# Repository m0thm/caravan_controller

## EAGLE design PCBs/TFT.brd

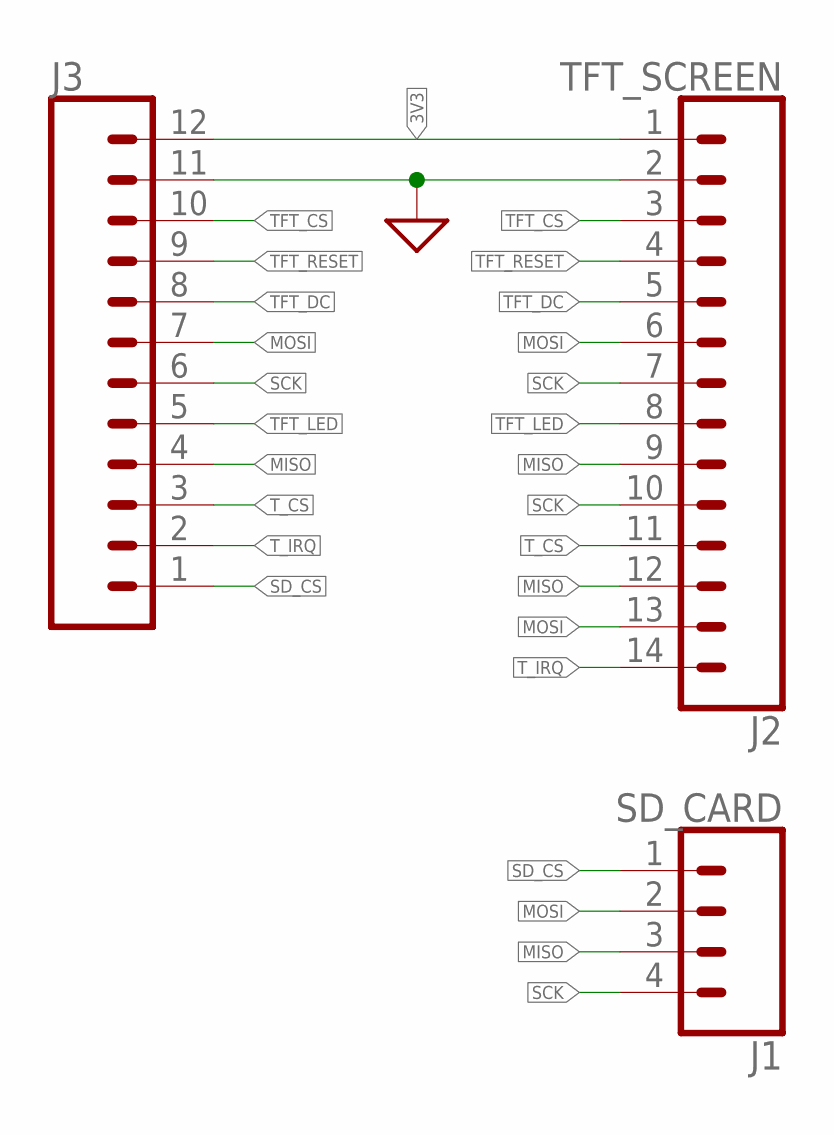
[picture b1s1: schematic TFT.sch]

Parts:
J1: SD_CARD; 1X04
J2: TFT_SCREEN; 1X14
J3: CONN_12; 1X12

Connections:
3V3: J2.1, J3.12
GND: J2.2, J3.11
MISO: J1.3, J2.9, J2.12, J3.4
MOSI: J1.2, J2.6, J2.13, J3.7
SCK: J1.4, J2.7, J2.10, J3.6
SD_CS: J1.1, J3.1
TFT_CS: J2.3, J3.10
TFT_DC: J2.5, J3.8
TFT_LED: J2.8, J3.5
TFT_RESET: J2.4, J3.9
T_CS: J2.11, J3.3
T_IRQ: J2.14, J3.2

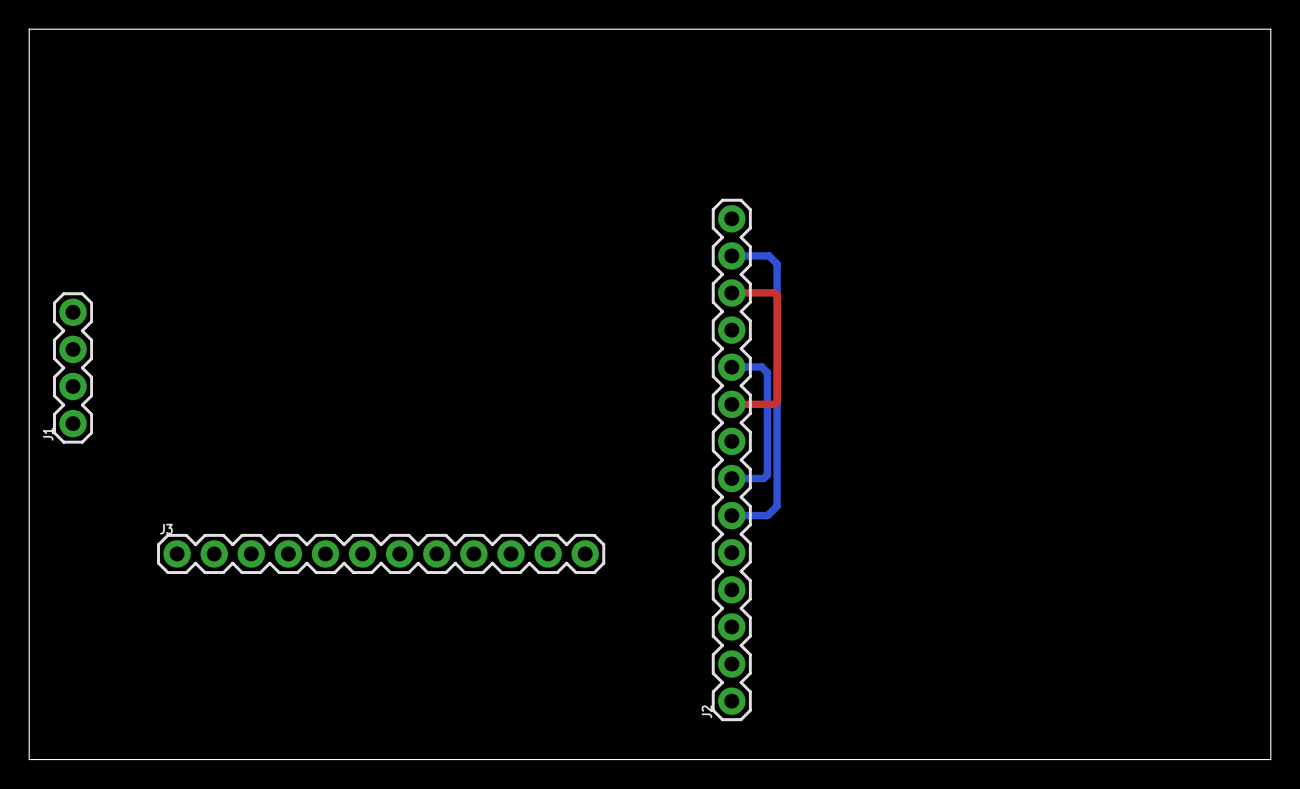
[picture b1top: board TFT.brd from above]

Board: 2 copper layers, 85.0 x 50.0 mm, 3 parts (0 on the bottom side), 12 nets.

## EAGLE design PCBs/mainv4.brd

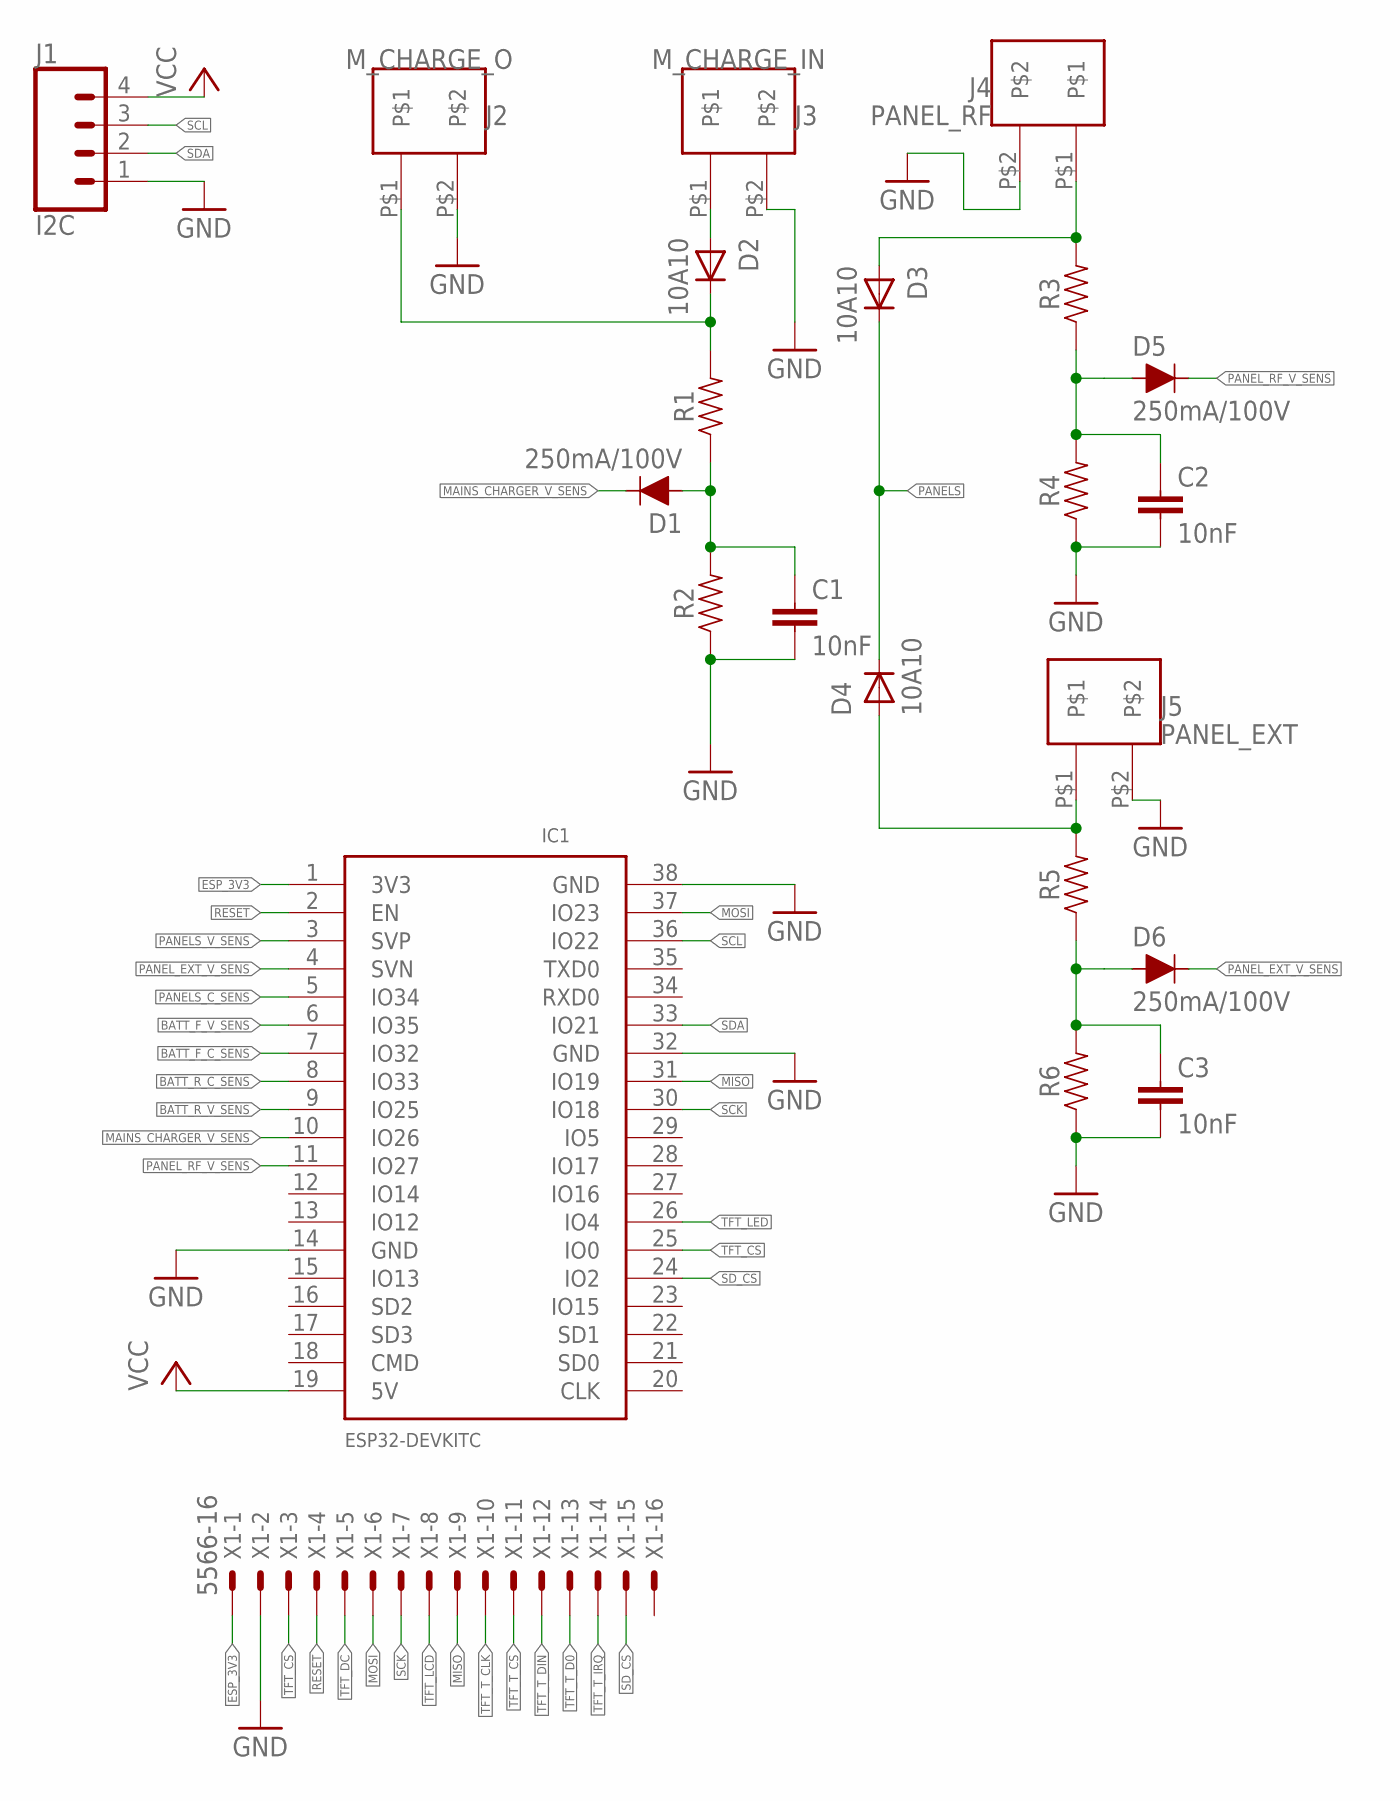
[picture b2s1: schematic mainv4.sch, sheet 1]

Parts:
C1, C2, C3: 10nF; 0603
D1, D5, D6: 250mA/100V; SOD-323
D2, D3, D4: 10A10; AG
IC1: ESP32DEVKITC; ESP32-DEVKITC
J1: I2C; MOLEX-1X4
J2: M_CHARGE_O; 40A-2PIN
J3: M_CHARGE_IN; 40A-2PIN
J4: PANEL_RF; 40A-2PIN
J5: PANEL_EXT; 40A-2PIN
R1, R2, R3, R4, R5, R6: 0805
X1: 5566-16

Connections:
BATT_F_C_SENS: IC1.7 (IO32); also elsewhere on the board
BATT_F_V_SENS: IC1.6 (IO35); also elsewhere on the board
BATT_R_C_SENS: IC1.8 (IO33); also elsewhere on the board
BATT_R_V_SENS: IC1.9 (IO25); also elsewhere on the board
ESP_3V3: IC1.1 (3V3), X1.1
GND: C1.2, C2.2, C3.2, IC1.14 (GND), IC1.32 (GND), IC1.38 (GND), J1.1, J2.P$2, J3.P$2, J4.P$2, J5.P$2, R2.1, R4.1, R6.1, X1.2; also elsewhere on the board
MAINS_CHARGER_V_SENS: D1.C, IC1.10 (IO26)
MISO: IC1.31 (IO19), X1.9
MOSI: IC1.37 (IO23), X1.6
unnamed: D2.A, J3.P$1
unnamed: D2.C, J2.P$1, R1.2
unnamed: D3.A, J4.P$1, R3.2
unnamed: C2.1, D5.A, R3.1, R4.2
unnamed: C3.1, D6.A, R5.1, R6.2
unnamed: D4.A, J5.P$1, R5.2
unnamed: C1.1, D1.A, R1.1, R2.2
PANELS: D3.C, D4.C; also elsewhere on the board
PANELS_C_SENS: IC1.5 (IO34); also elsewhere on the board
PANELS_V_SENS: IC1.3 (SVP); also elsewhere on the board
PANEL_EXT_V_SENS: D6.C, IC1.4 (SVN)
PANEL_RF_V_SENS: D5.C, IC1.11 (IO27)
RESET: IC1.2 (EN), X1.4
SCK: IC1.30 (IO18), X1.7
SCL: IC1.36 (IO22), J1.3
SDA: IC1.33 (IO21), J1.2
SD_CS: IC1.24 (IO2), X1.15
TFT_CS: IC1.25 (IO0), X1.3
TFT_DC: X1.5
TFT_LCD: X1.8
TFT_LED: IC1.26 (IO4)
TFT_T_CLK: X1.10
TFT_T_CS: X1.11
TFT_T_D0: X1.13
TFT_T_DIN: X1.12
TFT_T_IRQ: X1.14
VCC: IC1.19 (5V), J1.4; also elsewhere on the board

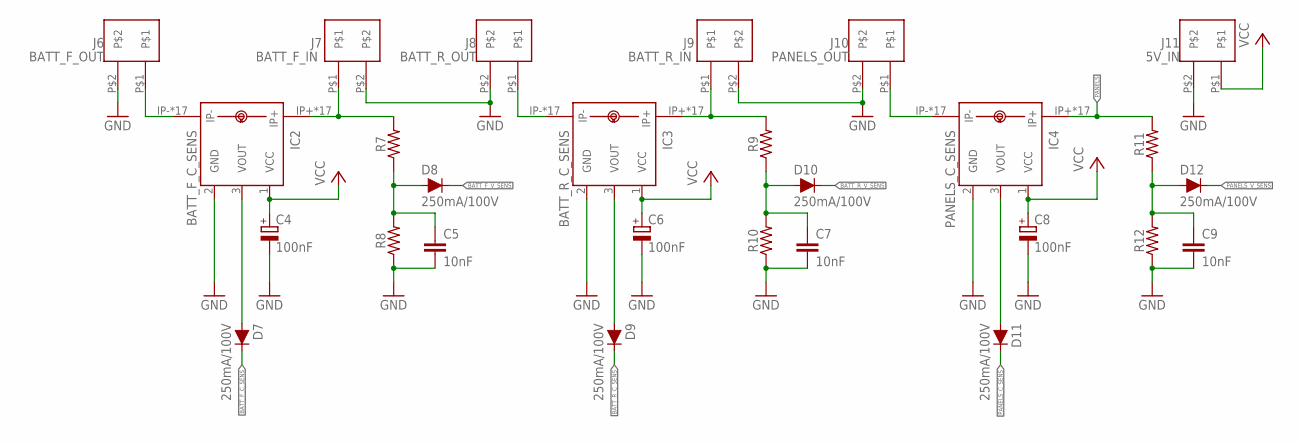
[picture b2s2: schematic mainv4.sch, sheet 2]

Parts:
C4, C6, C8: 100nF; PANASONIC_E
C5, C7, C9: 10nF; 0603
D7, D8, D9, D10, D11, D12: 250mA/100V; SOD-323
IC2: BATT_F_C_SENS; CB-PFF
IC3: BATT_R_C_SENS; CB-PFF
IC4: PANELS_C_SENS; CB-PFF
J6: BATT_F_OUT; 40A-2PIN
J7: BATT_F_IN; 40A-2PIN
J8: BATT_R_OUT; 40A-2PIN
J9: BATT_R_IN; 40A-2PIN
J10: PANELS_OUT; 40A-2PIN
J11: 5V_IN; 40A-2PIN
R7, R8, R9, R10, R11, R12: 0805

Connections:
BATT_F_C_SENS: D7.C; also elsewhere on the board
BATT_F_V_SENS: D8.C; also elsewhere on the board
BATT_R_C_SENS: D9.C; also elsewhere on the board
BATT_R_V_SENS: D10.C; also elsewhere on the board
GND: C4.-, C5.2, C6.-, C7.2, C8.-, C9.2, IC2.2 (GND), IC3.2 (GND), IC4.2 (GND), J6.P$2, J7.P$2, J8.P$2, J9.P$2, J10.P$2, J11.P$2, R8.1, R10.1, R12.1; also elsewhere on the board
unnamed: IC2.IP-, IC2.IP-@2 (IP-), IC2.IP-@3 (IP-), IC2.IP-@4 (IP-), IC2.IP-@5 (IP-), IC2.IP-@6 (IP-), IC2.IP-@7 (IP-), IC2.IP-@8 (IP-), IC2.IP-@9 (IP-), IC2.IP-@10 (IP-), IC2.IP-@11 (IP-), IC2.IP-@12 (IP-), IC2.IP-@13 (IP-), IC2.IP-@14 (IP-), IC2.IP-@15 (IP-), IC2.IP-@16 (IP-), IC2.IP-@17 (IP-), J6.P$1
unnamed: D7.A, IC2.3 (VOUT)
unnamed: IC2.IP+, IC2.IP+@2 (IP+), IC2.IP+@3 (IP+), IC2.IP+@4 (IP+), IC2.IP+@5 (IP+), IC2.IP+@6 (IP+), IC2.IP+@7 (IP+), IC2.IP+@8 (IP+), IC2.IP+@9 (IP+), IC2.IP+@10 (IP+), IC2.IP+@11 (IP+), IC2.IP+@12 (IP+), IC2.IP+@13 (IP+), IC2.IP+@14 (IP+), IC2.IP+@15 (IP+), IC2.IP+@16 (IP+), IC2.IP+@17 (IP+), J7.P$1, R7.2
unnamed: C5.1, D8.A, R7.1, R8.2
unnamed: D9.A, IC3.3 (VOUT)
unnamed: IC3.IP-, IC3.IP-@2 (IP-), IC3.IP-@3 (IP-), IC3.IP-@4 (IP-), IC3.IP-@5 (IP-), IC3.IP-@6 (IP-), IC3.IP-@7 (IP-), IC3.IP-@8 (IP-), IC3.IP-@9 (IP-), IC3.IP-@10 (IP-), IC3.IP-@11 (IP-), IC3.IP-@12 (IP-), IC3.IP-@13 (IP-), IC3.IP-@14 (IP-), IC3.IP-@15 (IP-), IC3.IP-@16 (IP-), IC3.IP-@17 (IP-), J8.P$1
unnamed: IC3.IP+, IC3.IP+@2 (IP+), IC3.IP+@3 (IP+), IC3.IP+@4 (IP+), IC3.IP+@5 (IP+), IC3.IP+@6 (IP+), IC3.IP+@7 (IP+), IC3.IP+@8 (IP+), IC3.IP+@9 (IP+), IC3.IP+@10 (IP+), IC3.IP+@11 (IP+), IC3.IP+@12 (IP+), IC3.IP+@13 (IP+), IC3.IP+@14 (IP+), IC3.IP+@15 (IP+), IC3.IP+@16 (IP+), IC3.IP+@17 (IP+), J9.P$1, R9.2
unnamed: C7.1, D10.A, R9.1, R10.2
unnamed: D11.A, IC4.3 (VOUT)
unnamed: IC4.IP-, IC4.IP-@2 (IP-), IC4.IP-@3 (IP-), IC4.IP-@4 (IP-), IC4.IP-@5 (IP-), IC4.IP-@6 (IP-), IC4.IP-@7 (IP-), IC4.IP-@8 (IP-), IC4.IP-@9 (IP-), IC4.IP-@10 (IP-), IC4.IP-@11 (IP-), IC4.IP-@12 (IP-), IC4.IP-@13 (IP-), IC4.IP-@14 (IP-), IC4.IP-@15 (IP-), IC4.IP-@16 (IP-), IC4.IP-@17 (IP-), J10.P$1
unnamed: C9.1, D12.A, R11.1, R12.2
PANELS: IC4.IP+, IC4.IP+@2 (IP+), IC4.IP+@3 (IP+), IC4.IP+@4 (IP+), IC4.IP+@5 (IP+), IC4.IP+@6 (IP+), IC4.IP+@7 (IP+), IC4.IP+@8 (IP+), IC4.IP+@9 (IP+), IC4.IP+@10 (IP+), IC4.IP+@11 (IP+), IC4.IP+@12 (IP+), IC4.IP+@13 (IP+), IC4.IP+@14 (IP+), IC4.IP+@15 (IP+), IC4.IP+@16 (IP+), IC4.IP+@17 (IP+), R11.2; also elsewhere on the board
PANELS_C_SENS: D11.C; also elsewhere on the board
PANELS_V_SENS: D12.C; also elsewhere on the board
VCC: C4.+, C6.+, C8.+, IC2.1 (VCC), IC3.1 (VCC), IC4.1 (VCC), J11.P$1; also elsewhere on the board

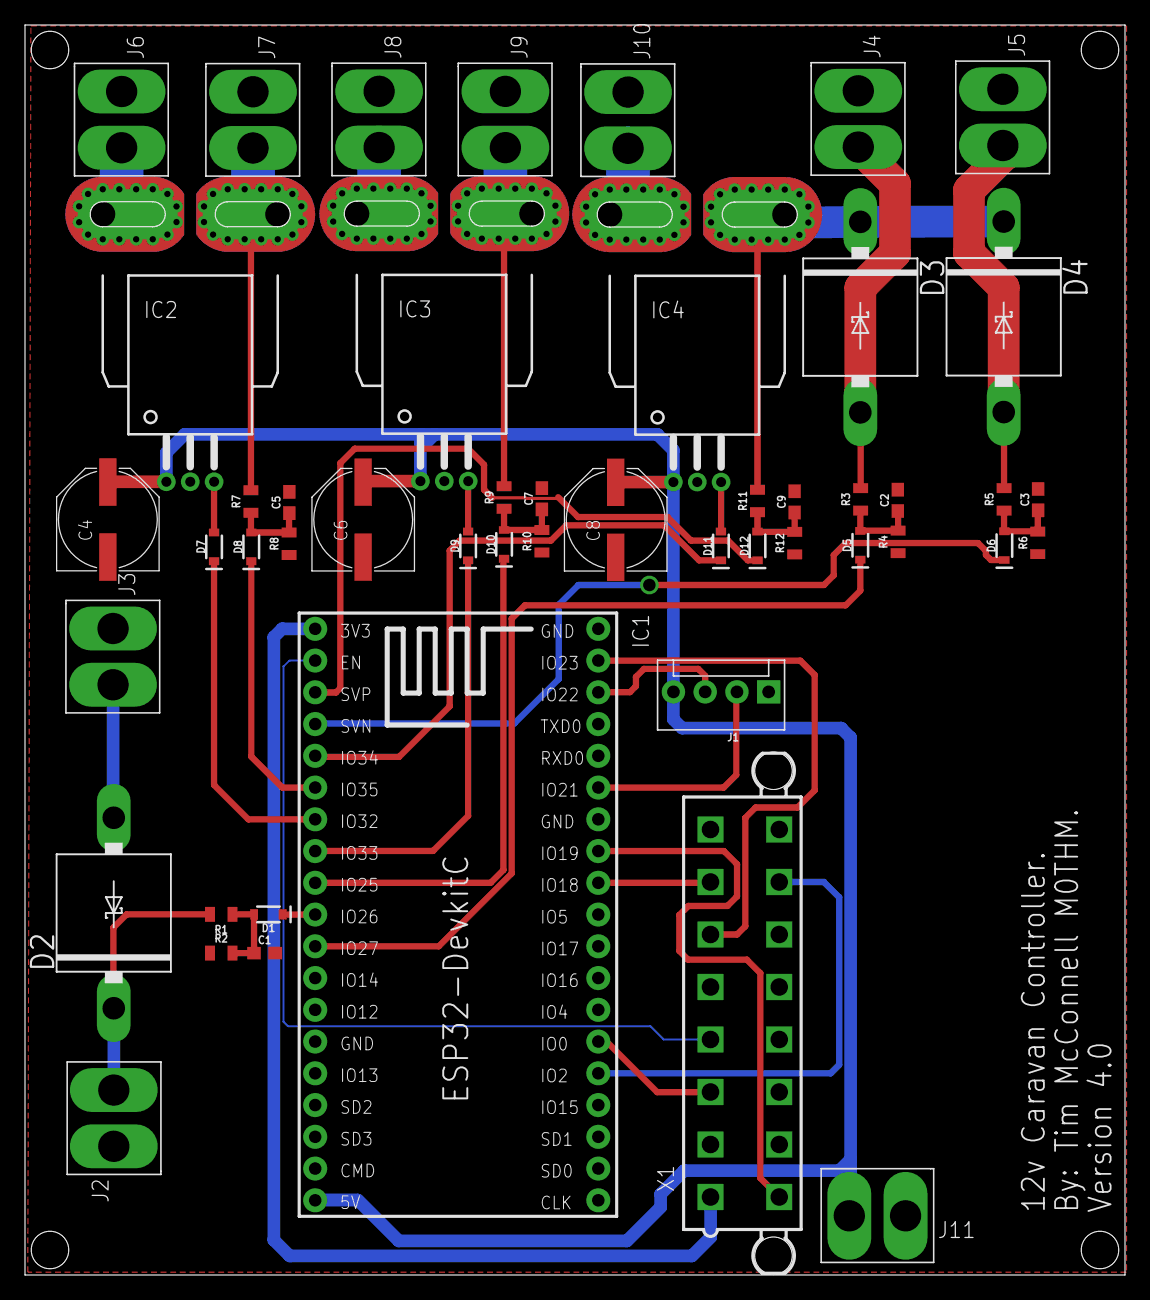
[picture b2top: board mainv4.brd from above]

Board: 2 copper layers, 88.0 x 100.0 mm, 49 parts (0 on the bottom side), 39 nets.

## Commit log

2018-10-31 Init
    Init

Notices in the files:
parts and their libraries:
SparkFun-Connectors: Licensing: Creative Commons ShareAlike 4.0 International - https://creativecommons.org/licenses/by-sa/4.0
